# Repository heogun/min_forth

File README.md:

# min_forth

Minimal 64x4 (Revision 1.4 Redux) 홈 컴퓨터용 **16비트 Forth 커널**과, 그 하드웨어를 사이클 단위로 재현하는 **Rust 에뮬레이터** 저장소.

## 구성

| 경로 | 내용 |
| --- | --- |
| `minforth/forth/kernel.fs` | Forth 커널 본체. 호스트 Forth가 아니라 프로젝트 전처리기를 쓰는 어셈블리 소스 |
| `minforth/tools/` | C++ 어셈블러(`asm.cpp`), 이미지 빌더(`build.py`), 보조 스크립트 |
| `minforth/test/` | 커널 검증용 `.fs` 프로그램 |
| `minimal64/Revision 1.4 Redux/FLASH Images/` | ISA 결함 3건을 수정한 ROM이 기존 위치에 직접 설치됨. 실행·빌드·검증의 단일 기준 |
| `minredux/` | 외부 crate 의존성 없는 흑백 기준 Rust 에뮬레이터, ISA/화면 회귀 스크립트 |
| `minredux/gui/` | `minredux` 코어를 사용해 400x240 VRAM을 직접 렌더링하는 창 기반 흑백 프론트엔드 |
| `minredux-cs/` | 컬러 + SN76489 통합안(CS-DRAFT-1)용 Rust 에뮬레이터. `minredux/`를 기반으로 확장 |
| `benchmarks/` | Min 인터프리터와 Forth의 동일 알고리즘 실행 비용 비교 하네스 |
| `AGENTS.md` | 작업 공간 규칙과 커널 불변식 |
| `PROGRESS.md`, `benchmark.md` | 구현 이력, 벤치마크 방법과 결과 |

`minimal64/`(수정 ROM·MinOS·마이크로코드)와 `extended-min/`(별도 Min 인터프리터)은 각자의 저장소에서 관리되며 이 저장소에는 포함하지 않는다. 삭제된 원본 ROM이나 별도 `roms/` 번들은 필요 없다. 위 기본 경로에 수정 이미지와 일치하는 CSV가 있어야 하며 `python3 minredux/verify_rom.py`로 검증한다.

## 빌드

```sh
# 네이티브 어셈블러 (최초 1회, 또는 asm.cpp 수정 후)
clang++ -O2 -std=c++11 minforth/tools/asm.cpp -o minforth/tools/asm

# Forth 커널 이미지: minforth/build/flash.bin 생성
python3 minforth/tools/build.py minforth/forth/kernel.fs minforth 0x1000
```

`build.py`는 `forth/defs.inc`를 앞에 붙이고 매크로/인클루드를 전개한 뒤, 목적지 인자와 일치하는 `#org`를 요구하고 결과를 MinOS 플래시 파일 시스템에 삽입한다. 참조 ROM을 건드리지 않으려면 `--out DIR`을 쓴다.

## 실행과 검증

```sh
cd minredux
cargo build --release

python3 regress.py                      # 커널 end-to-end 회귀
python3 runline.py ': t 0 10 0 DO I + LOOP . ;' 't'
./target/release/minredux term --rom-dir ../minforth/build   # Ctrl-] 로 종료
```

Python 도우미는 실행 파일과 ROM을 자동으로 다시 빌드하지 않으므로, 어셈블리나 Rust 소스를 고친 뒤에는 위 빌드 단계를 먼저 실행한다.

터미널 대신 실제 400x240 화면을 창에서 보려면 `minredux/gui`를 실행한다.
Enter를 LF `0x0a`, Backspace를 `0x08`로 보내므로 터미널의 CR/DEL 불일치가 없다.

```sh
cd minredux/gui
cargo run --release
cargo run --release -- --rom-dir ../../minforth/build   # Forth 커널
```

컬러·SN76489 통합안은 `cd minredux-cs`에서 같은 방식으로 빌드·회귀하며, 추가로
`--ansi`, `--ppm`, `--wav` 출력을 지원한다. 자세한 내용은
[`minredux-cs/README.md`](minredux-cs/README.md)를 참고한다.

## 문서

- Minimal 64x4 원작자(slu4) 매뉴얼 사본: [`docs/manual.txt`](docs/manual.txt)
- 실물 제작 부품 구매 목록과 주의사항: [`docs/HARDWARE_SHOPPING.md`](docs/HARDWARE_SHOPPING.md)
- 커널 설계와 `ABORT"` 동작: [`minforth/README.md`](minforth/README.md)
- 흑백 기준 에뮬레이터 사용법과 정확도 범위: [`minredux/README.md`](minredux/README.md)
- 흑백 GUI 프론트엔드: [`minredux/gui/README.md`](minredux/gui/README.md)
- 컬러·SN76489 에뮬레이터와 한계: [`minredux-cs/README.md`](minredux-cs/README.md)
- ISA 검증 내역: [`minredux/ISA_VALIDATION.md`](minredux/ISA_VALIDATION.md)
- 벤치마크 하네스: [`benchmark.md`](benchmark.md)
- Cycle-exact 제안과 타당성 검토: [`CYCLE_EXACT_ROADMAP.md`](CYCLE_EXACT_ROADMAP.md), [`CYCLE_EXACT_REVIEW.md`](CYCLE_EXACT_REVIEW.md) (구현 승인/실기 검증 완료를 뜻하지 않음)

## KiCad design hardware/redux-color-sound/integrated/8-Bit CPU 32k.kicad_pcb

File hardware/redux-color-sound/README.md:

# Redux 1.4 — Attribute Color + SN76489 통합 보드

상태: **컬러·SN76489 통합 회로도와 PCB 부품/net 배치 초안이 추가됨. 배선·최악 조건 타이밍 검증 미완료, 제조 금지.**

실제 추가 회로와 현재 검증 상태: **[CIRCUIT.md](CIRCUIT.md)**.
KiCad에서는 `integrated/8-Bit CPU 32k.kicad_pro`를 연다.
`cad/`는 경고를 해결한 기존 흑백 보드 기준본이며, 추가 회로가 있는 프로젝트와 구분한다.

2026-10-30 사용자 선택: 기존 Revision 1.4 Redux를 기반으로 컬러와
SN76489 음원을 하나의 새 PCB에 통합한다. 원본 `minimal64/`는 변경하지 않는다.
이 문서는 실기 동작, 타이밍 여유, 제조 가능성을 보증하지 않는다.

## 1. 범위와 불변 조건

- CPU 8MHz, 기존 명령·마이크로코드 실행 사이클을 유지한다.
- 컬러·음원 때문에 CPU 클록을 게이팅하거나 WAIT/DMA를 추가하지 않는다.
- 기존 비트맵 접근 대역폭을 색상 읽기로 나눠 쓰지 않는다.
- 400×240 표시, 기존 PS/2·UART·확장 포트를 유지한다.
- 컬러는 1bpp 비트맵 + 영역별 전경/배경 각 16색이다. 픽셀별 독립 4bpp가 아니다.
- 음원은 SN76489 계열 전용 IC를 사용한다. AY, TTS, SD, 조이스틱은 이번 범위 밖이다.
- DIP/관통형 중심을 유지하되, 정확한 주문번호·소켓·풋프린트는 회로도 확정 후 결정한다.
- 리셋 중/후 컬러 비활성 및 하드웨어 오디오 mute를 목표로 한다.

무대기 CPU와 무제한 주변장치 쓰기는 다르다. 음원·Attribute 쓰기 간격과
pending 데이터의 수명은 소프트웨어가 지켜야 한다. 폴링·지연 명령을 사용하면
그 프로그램의 CPU 시간은 소비된다. 모든 전송을 CPU 비용 없이 처리한다는 뜻이 아니다.

## 2. 확인한 기준 자료

### Redux

- 로컬 원본 저장소 커밋: `1a59c95695d1a6a6147584465ee87803fe9387da`.
- `minimal64/Revision 1.4 Redux/Schematics.pdf`: Control Logic, Memory and MAR, VGA.
- `minimal64/Revision 1.4 Redux/KiCAD9/`: 기존 KiCad 9 프로젝트.
- `minimal64/Revision 1.4 Redux/Programs/asm/vga.asm`: ViewPort `0x430c`.
- `minredux/src/lib.rs`: 64바이트 stride, ViewPort `(96,12)`, 400×240 crop.

기존 VGA는 U36 AS6C62256, U35 HC166, U37/U39 HC590, U38/U40/U41 HC574를 쓴다.
영상 읽기 예약 구간과 CPU 영상 쓰기를 유지하면서 색상 RAM을 병렬 읽는 방향이다.
`~VGA_GET` 종료 시 스캔 카운터도 갱신되므로 같은 에지에서 색상을 무심코
래치하면 다음 바이트 주소/현재 픽셀 간 정렬 문제가 생길 수 있다.

### SN76489 참고 보드

[hans61/Minimal-64x4-Expansion](https://github.com/hans61/Minimal-64x4-Expansion),
검토 커밋 `92207bfac9450aeef2b72a4420adfdd4c44e60af`:

- `hardware/Rev.6/README.md`: 주소 배치와 과거 제어 신호 오류 설명.
- `hardware/Rev.7/eagle/expansion-sn76489-kempton-sd-rev7.sch`: Eagle XML의 부품·net 연결 확인.
- `software/sn76489/BirdSound.asm`: 데이터 기록 후 제어 bit 1 assert/deassert 순서 확인.

확인 사항:

- `0xFEE0` 데이터 HC574, `0xFEE2` 제어 HC173, 제어 bit 1로 음원 쓰기를 제어한다.
- 실제 음원 `~CE`는 GND, HC173 Q2를 HC04로 반전한 신호가 `~WE`로 들어간다.
- CPU bit 0은 SN의 **D7**, CPU bit 7은 SN의 **D0**에 연결된다.
  TI 표기의 D0가 MSB이므로 이름만 보고 같은 번호끼리 연결하면 안 된다.
- 원문은 초기 리비전의 HC74 기반 CS 제어에 드문 오류가 있었으며 Rev.6에서
  HC173으로 바꿨다고 설명한다. 이전 회로로 단순화하지 않는다.
- 음원 경로의 부품 종류: HC30, HC04, HC11, HC138, HC574, HC173, SN76489,
  LM386. 다른 기능을 제외해도 **앰프 포함 8개 IC + 발진기 모듈**인 참고 구조다.
  이는 통합 보드의 확정 BOM이나 최소 칩 수 증명이 아니다.
- 4MHz/3.579MHz 별도 발진기와 확장 포트 클록을 선택하는 연결이 있다.
  원본 보드용 소프트웨어의 NOP 시간은 Redux에 그대로 적용하지 않는다.

[TI SN76489AN 데이터시트 사본](https://map.grauw.nl/resources/sound/texas_instruments_sn76489an.pdf):
5V, 최대 4MHz, open-collector READY, 대략 32 입력 클록의 데이터 처리,
D0=MSB를 확인할 기준이다. SN76494 등은 같은 조건으로 대체하지 않는다.
최종 설계 전에 정확한 구매 칩의 데이터시트 전체 타이밍 표/파형을 확인한다.

[michaelkamprath/minimal-64x4-expansion-cards](https://github.com/michaelkamprath/minimal-64x4-expansion-cards)는
TMS5220C 음성 합성·곱셈기·타이머의 참고 자료다. SN 음원이나 컬러 회로의
검증 자료로 취급하지 않는다. 이번 초안에는 외부 회로 파일을 복사하지 않았다.

## 3. 컬러 주소와 화면 좌표

내부 VRAM은 512×256에 해당하는 **16KB** 비트맵 공간이다.
U36의 부품 용량이 32KB인 것과 실제 연결된 주소 공간은 구분한다.
표시/소프트웨어 ViewPort는 그 안의 `(96,12)`에서 시작하는 400×240 영역이다.

Attribute는 64열×32행, **2KB**, 한 바이트에 `background[7:4] | foreground[3:0]`.
별도 SRAM 한 개를 사용하고 CPU RAM/비트맵을 대신 사용하지 않는다.

**권장 주소식: 글자 행과 일치하도록 세로 위상 +4 (mod 256)**

```text
x, y       = 내부 비트맵 좌표 (0..511, 0..255)
attr_x     = x >> 3
attr_y     = ((y + 4) & 255) >> 3
attr_index = attr_y * 64 + attr_x       # 0..2047

ViewPort 글자 (column, row), column=0..49, row=0..29:
attr_index = (row + 2) * 64 + column + 12
```

이렇게 하면 400×240 화면의 50×30개 8×8 글자 영역과 색상이 일치한다.
보이는 1,500개 Attribute는 2KB 배열 안에서 stride 64로 배치된다.
자동으로 연속된 1,500바이트가 되는 것은 아니다.

단순히 `y >> 3`만 배선하면 ViewPort가 y=12에서 시작하기 때문에 31개
Attribute 행에 걸치고 글자 중간에서 색이 바뀐다. 앞선 단순 50×30 설명에는
이 위상 보정 조건이 빠져 있었다. 보정 로직의 지연·칩 수를 BOM에 포함해야 한다.

### 영상 데이터 경로

```text
스캔 주소 ─┬─ 기존 VRAM → 기존 HC166 → pixel ──────────┐
           └─ Attribute 주소 → SRAM → 색상 레지스터 ──┤
                                                     ↓
                                    전경/배경 선택 → blanking → RGB DAC
CPU → 주소/데이터 유지 → 영상 읽기 외 구간에 Attribute 쓰기
```

- SRAM 읽기는 기존 비트맵 읽기와 병렬 수행한다. 픽셀마다 SRAM을 읽지 않는다.
- 색상 레지스터는 CPU SRAM 쓰기 중에도 현재 출력 색상을 유지한다.
- 읽기/쓰기 주소 MUX, 데이터 래치, pending 제어가 필요하다.
- 새 Attribute 요청이 미처리 요청을 덮어쓰지 않도록 최소 간격 또는 상태 읽기를 정의한다.
- CPU 쓰기 시점과 SRAM commit이 달라질 경우 주소와 데이터가 함께 보존되어야 한다.
- 실제 추가 회로는 기존 VREG의 주소·데이터 유지 및 영상 쓰기 slot을 공유한다.
  제어 bit 2로 비트맵/Attribute 쓰기를 선택하고, 쓰기 캡처 시 plane도 함께 저장한다.
- SRAM 전원 투입 내용은 미정이다. 초기화 전에는 컬러 출력을 활성화하지 않는다.
- 비표시 구간은 모든 RGB를 검정으로 강제한다. HSYNC/VSYNC만으로 active-video를
  판정하거나 기존 VRAM의 0 데이터를 검정 대신 사용하지 않는다.
- ViewPort 외 테두리 색상을 허용할지는 미정이다. 400×240 crop을 곧바로
  회로의 실제 수평·수직 blanking 경계라고 가정하지 않는다.
- RGBI 계열 고정 16색 DAC를 기본 후보로 한다. CGA의 정확한 갈색 보정/색상표
  호환은 아직 약속하지 않는다. 75Ω 부하에서 0..약 0.7V를 검증해야 한다.

## 4. SN76489 데이터 경로

```text
CPU BUS → HC574 데이터 래치 → SN76489 → AC 결합/볼륨 → 오디오 출력
CPU 제어 쓰기 → 리셋 가능한 제어 레지스터 → ~WE
독립 발진기 → SN CLK
```

- 5V DIP-16 SN76489AN을 우선 검토 대상으로 한다. 계열 내 다른 칩은 재검토한다.
- 독립 **3.579545MHz 발진기**를 우선 후보로 한다. 4MHz 기준 음악 데이터는
  음높이 값을 변환해야 한다. 기존 CPU 클록선을 음원 부하로 직접 사용하지 않는다.
- `f = clock / (32 * N)`, 일반 톤 주기 `N=1..1023`. N=0 및 잡음 동작은 별도 검증한다.
- 데이터 유지 → 쓰기 assert → 처리 완료 → 쓰기 deassert → 다음 데이터 순서로 제어한다.
- 약 32클록은 설계 참고값일 뿐 보증 최대 지연이 아니다. 정확한 칩의 READY/파형과
  여유를 검토해 쓰기 폭 및 다음 전송 조건을 확정한다.
- READY를 CPU 클록/WAIT에 연결하지 않는다. 사용한다면 pull-up 및 TTL→HC 입력
  임계값 적합성을 확인하고, 소프트웨어 상태 입력으로 읽도록 한다.
- 단일 래치는 FIFO가 아니다. 전송 중 데이터 갱신 금지 조건을 드라이버에 명시한다.
- SN에는 시스템 reset으로 모든 음량을 확실히 지우는 인터페이스가 없으므로,
  부팅 시 소프트웨어가 `0x9f, 0xbf, 0xdf, 0xff`를 보내기 전까지 아날로그 경로를
  하드웨어 mute한다. 제어 래치만 초기화해서 무음을 보장한다고 주장하지 않는다.
- 기본 출력은 외부 앰프에 연결 가능한 오디오 출력을 우선 검토한다.
  온보드 LM386 스피커 앰프는 선택 실장 후보이며, 헤드폰 출력과 동일시하지 않는다.

## 5. 주소 배치 — 추가 회로 초안

기존 참고 보드와의 음원 제어 관례를 일부 유지할 후보:

| 주소 | 후보 역할 |
| --- | --- |
| `0xFEE0` | 음원 데이터 래치 |
| `0xFEE1` | 상태 읽기 — READY/Attribute mode/color enable/audio enable |
| `0xFEE2` | 제어 레지스터 — bit 0 컬러, bit 1 음원 write, bit 2 Attribute mode, bit 3 unmute |
| `0xFEE3` | 미할당, 참고 보드 SPI와 겹치므로 함부로 재사용하지 않음 |
| `0xFEE4` | 예약 — 초기의 간접 주소 포트안은 채택하지 않음 |
| `0xFEE5` | 예약 |
| `0xFEE6` | 예약 |
| `0xFEE7` | 미할당 |

- 자동 증가·Attribute CPU read-back은 기본 요구사항에 넣지 않는다. 필요 시 비용 평가한다.
- `0xFEE8..0xFEEF`는 bit 3 미디코딩 alias다. 실제 RAM 제외 범위는 `0xFEE0..0xFEEF`다.
- 초기안과 달리 Attribute는 제어 bit 2를 설정하고 기존 `0x4000..0x7fff` VREG 창으로 쓴다.
- MinOS·Forth dictionary/프로그램은 I/O 16바이트를 RAM으로 사용하면 안 된다.
  새 메모리맵의 펌웨어 지원은 아직 추가하지 않았다. 에뮬레이터는
  `minredux-cs/`에 디지털 모델로 추가했다.
- 외부 확장 카드가 같은 주소를 선택하면 충돌한다. 온보드 I/O disable 수단을 고려한다.

## 6. 배치·검증 조건

- Attribute SRAM/색상 래치는 VGA 가까이, 음원/아날로그 출력은 보드 가장자리에 배치한다.
- CPU critical path는 유지하고 신규 팬아웃의 용량·배선 길이를 평가한다.
- 각 IC에 로컬 decoupling, 음원/앰프에는 적절한 bulk capacitor와 전원 필터를 둔다.
  아날로그/디지털 접지면을 무조건 분리하지 말고 연속된 귀환 경로를 확보한다.
- 신규 참조번호는 원본 IC와 충돌하지 않는 범위로 배정한다. 원본 번호는 가능한 보존한다.
- CPU 클록, VGA_GET, SRAM WE/OE, 색상 latch clock, pixel, SN clock/WE/READY에 테스트 포인트.
- 리셋·브라운아웃·부분 실장 시 컬러/mute 상태를 검증한다.
- 수정 제어 ROM 경로/검증은 기존 `docs/HARDWARE_SHOPPING.md`를 따른다.

### 제조 전 통과해야 할 항목

1. 실제 회로도와 정확한 부품/데이터시트/풋프린트 확정.
2. 주소 decode·INH·bank·버스 방향/tri-state truth table 검증.
3. SRAM 주소 MUX→읽기→색상 latch와 카운터 전환의 worst-case setup/hold 계산.
4. 비트맵과 색상의 첫/마지막 픽셀 정렬, Attribute 행 위상, blanking 검증.
5. Attribute 쓰기 중 표시 안정성·요청 유실·최대 갱신율 검증.
6. SN 쓰기 타이밍, 데이터 bit 순서, TTL/CMOS 경계, 리셋 mute 검증.
7. 에뮬레이터/논리 모델 확장 및 기존 CPU 회귀 검사. 이것만으로 전기 검증을 대체하지 않음.
8. KiCad ERC/DRC, netlist 대조, 커넥터·패키지 치수 검사.
9. 전류 예산, VGA 75Ω 출력, 오디오 출력 부하 검토.
10. 시제품에서 오실로스코프 실측과 장시간 CPU/영상/음원 동시 동작 시험.

첫 주문은 검증용 시제품이다. 실기 시험 전 상태를 양산 검증 완료로 표시하지 않는다.

## 7. 현재 산출물과 남은 작업

- 완료: 요구사항, 참고 net 연결 검토, 좌표 보정식, 주소/인터페이스 후보 정리.
- 완료: [수정 CAD 작업본](cad/PROVENANCE.md)의 ERC·DRC·패리티 0건,
  기존 DRC 제외 항목 제거, 원본 회로 연결·동박 형상 보존 검사.
  KiCad에서는 `cad/8-Bit CPU 32k.kicad_pro`를 연다.
- 완료: 실제 통합 회로도 5개 sheet, PCB 부품·pad/net 반영, 추가 BOM 초안,
  디지털/정적 테스트 33개. 주소 디코드는 ATF22V10C 한 개(U64)로 바꿨다. Attribute 행 주소는 VA 버스 앞에서 계산한다(U66, R37–R41). 클록은 U67/U68로 분리했다. [현재 상태](CIRCUIT.md)를 참고한다.
- 에뮬레이터 기준 완료: Forth 커널 단어(`COLOR`, `AUDIO`, `ATTR!`, `ATTRFILL`, `SN!`,
  `TONE`, `VOL`, `NOISE`, `SILENCE`). [`../../minforth/README.md`](../../minforth/README.md)를 참고한다.
  `CIRCUIT.md`의 SN 쓰기 순서를 따르며, 실제 칩 타이밍으로는 검증하지 않았다.
- 타이밍 검토(2026-11-24): [TIMING_REVIEW.md](TIMING_REVIEW.md). 디코드 경로와 Attribute 주소 경로를
  고친 뒤 다시 계산해야 한다.
- 미완료: 추가 회로 배선, 최종 배치, 수정 회로의 타이밍 재검증,
  MinOS 수준 지원 및 실기 검증. 에뮬레이터 디지털 모델은
  [`../../minredux-cs/`](../../minredux-cs/)에 추가했으며, 이는 회로·실기 검증을
  대체하지 않는다.
- KiCad 10.0.7 설치 후 원본 CAD의 ERC/DRC/회로도 parity 기준 검사를 실행했다.
  결과와 재현 방법은 [KICAD_BASELINE.md](KICAD_BASELINE.md)를 참고한다.
  수정 기준 작업본도 같은 도구로 검사했다. 통합 회로도·PCB 검증이나 제조 출력이 완료된 것은 아니다.
- 원본 보드 회로도에 표기된 CC BY-NC-SA 4.0 고지와 외부 프로젝트의 권리 조건을
  파생 CAD 배포 전에 확인·보존한다. hans61 저장소의 공개 접근을 재배포 허가로
  간주하지 않는다. 라이선스 확인 전 회로 파일을 통째로 복사해 배포하지 않는다.

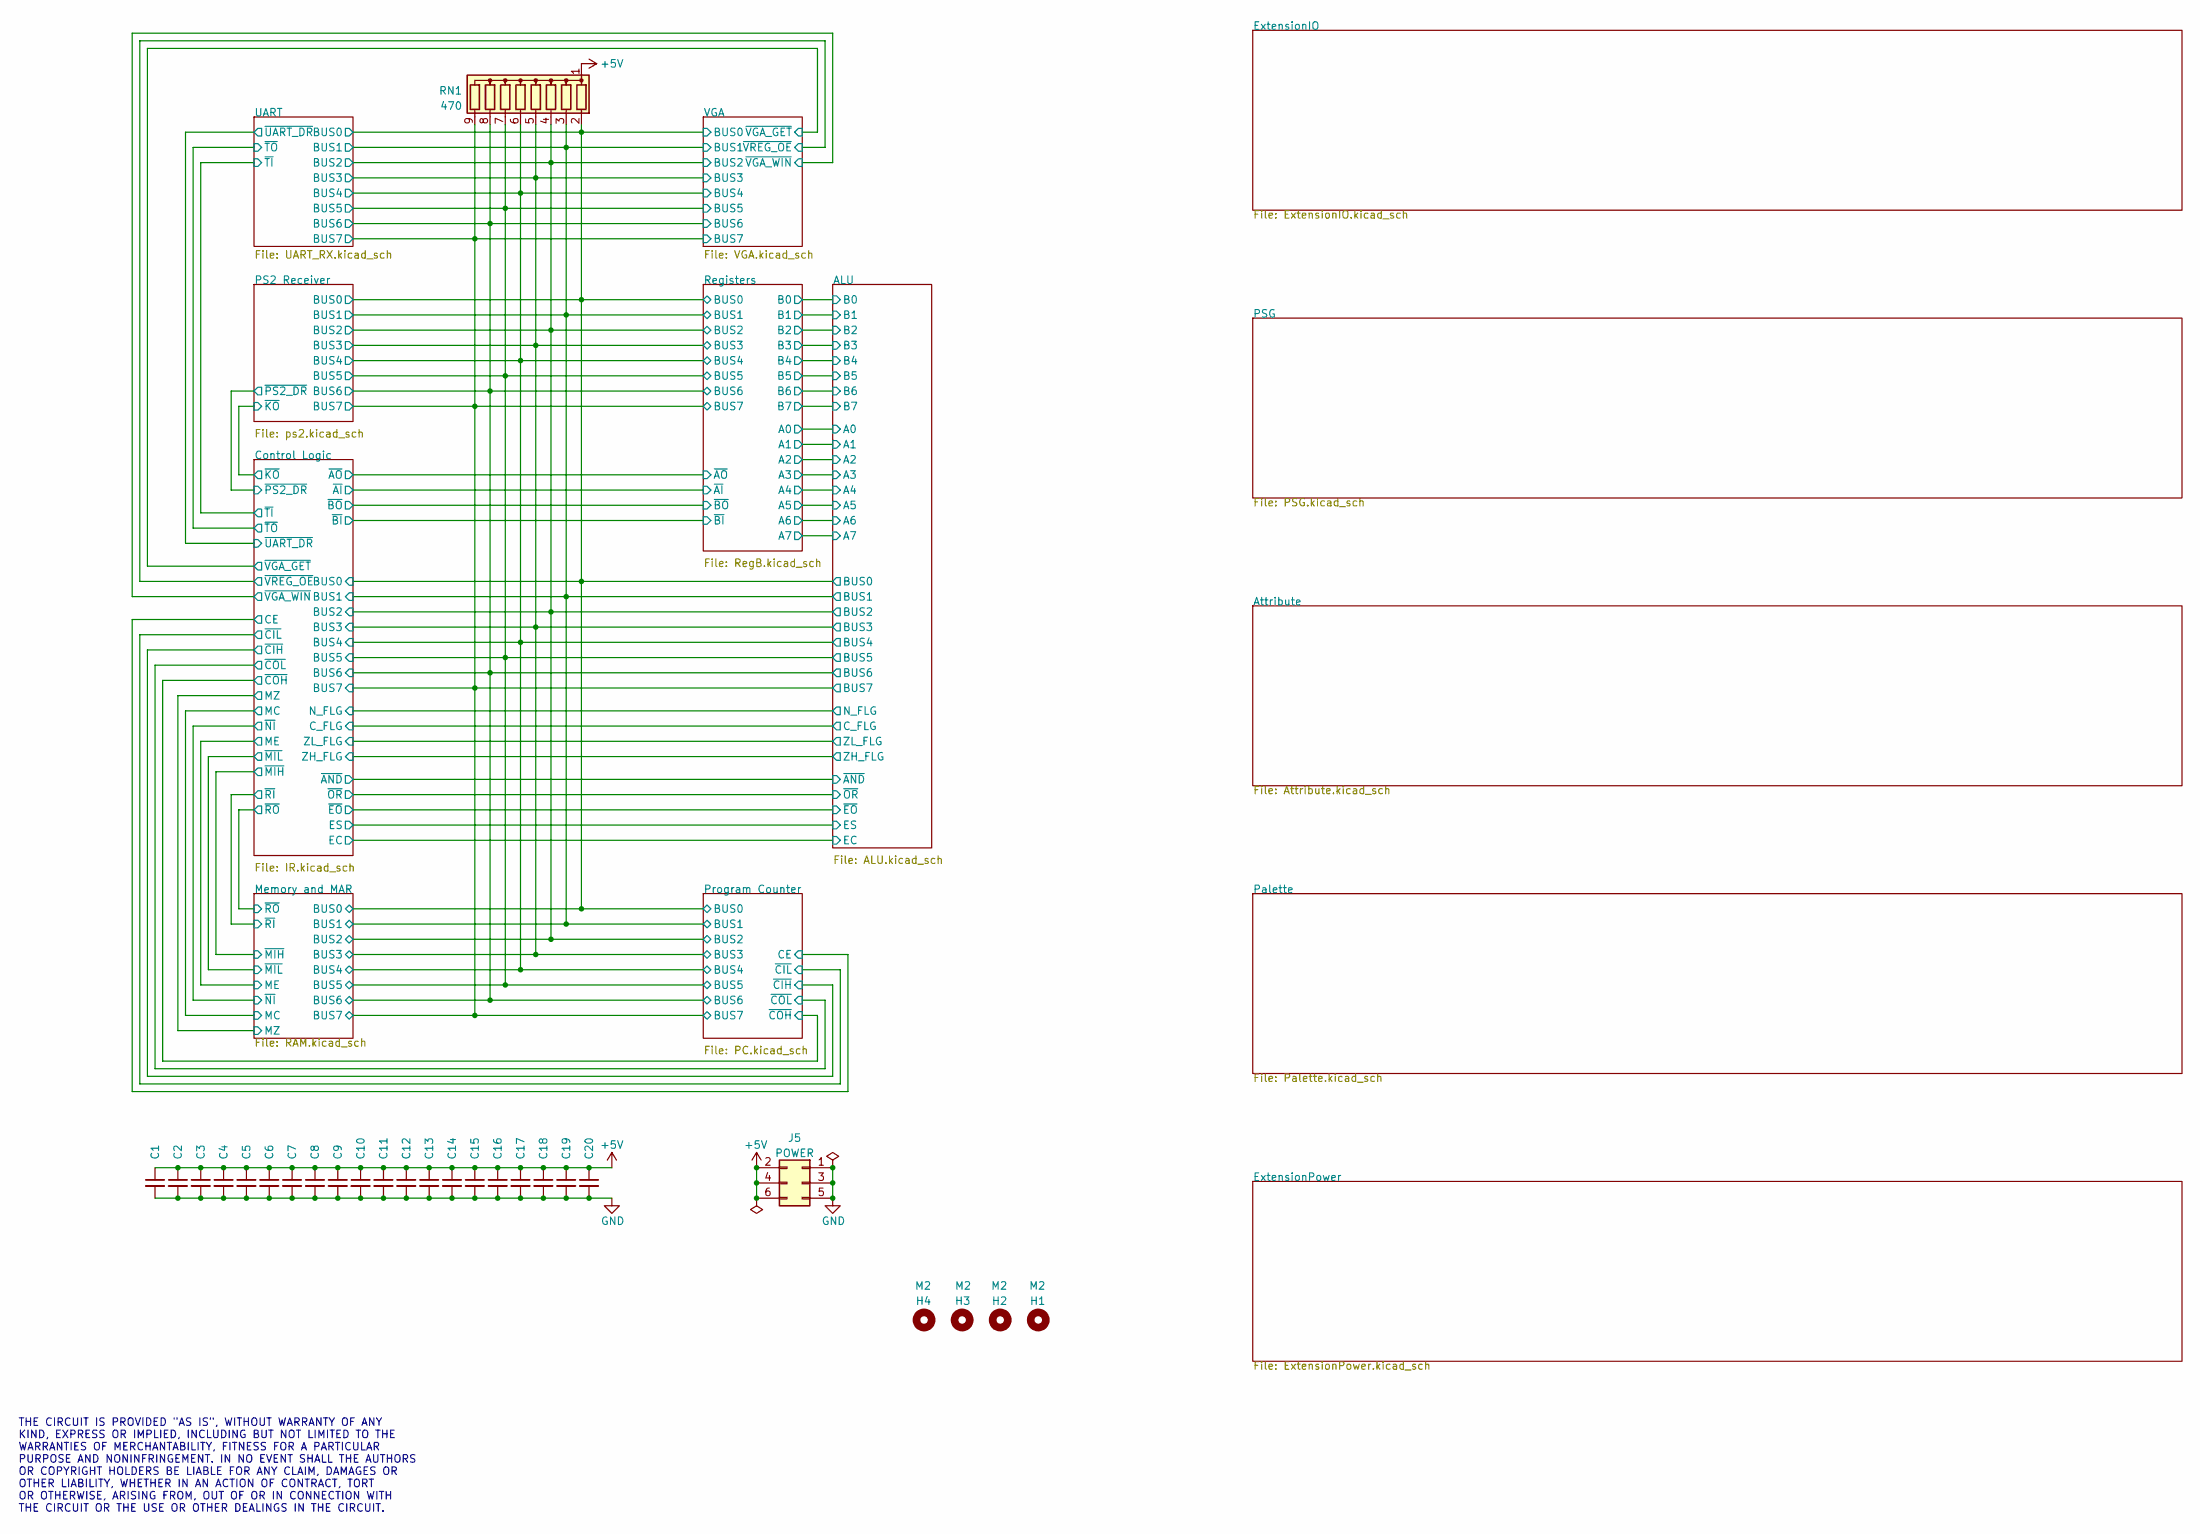
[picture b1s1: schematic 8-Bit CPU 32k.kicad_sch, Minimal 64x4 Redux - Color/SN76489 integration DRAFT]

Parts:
C1, C2, C3, C4, C5, C6, C7, C8, C9, C10, C11, C12, C13, C14, C15, C16, C17, C18, C19, C20: 100nF; C_Disc_D3.4mm_W2.1mm_P2.50mm
H1, H2, H3, H4: M2; MountingHole_2.2mm_M2
J5: POWER; PinSocket_2x03_P2.54mm_Vertical
RN1: 470; R_Array_SIP9

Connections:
+5V: C1.1, C2.1, C3.1, C4.1, C5.1, C6.1, C7.1, C8.1, C9.1, C10.1, C11.1, C12.1, C13.1, C14.1, C15.1, C16.1, C17.1, C18.1, C19.1, C20.1, J5.2, J5.4, J5.6, RN1.1 (common); also elsewhere on the board
BUS0: RN1.2 (R1); also elsewhere on the board
BUS1: RN1.3 (R2); also elsewhere on the board
BUS2: RN1.4 (R3); also elsewhere on the board
BUS3: RN1.5 (R4); also elsewhere on the board
BUS4: RN1.6 (R5); also elsewhere on the board
BUS5: RN1.7 (R6); also elsewhere on the board
BUS6: RN1.8 (R7); also elsewhere on the board
BUS7: RN1.9 (R8); also elsewhere on the board
GND: C1.2, C2.2, C3.2, C4.2, C5.2, C6.2, C7.2, C8.2, C9.2, C10.2, C11.2, C12.2, C13.2, C14.2, C15.2, C16.2, C17.2, C18.2, C19.2, C20.2, J5.1, J5.3, J5.5; also elsewhere on the board

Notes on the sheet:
THE CIRCUIT IS PROVIDED "AS IS", WITHOUT WARRANTY OF ANY KIND, EXPRESS OR IMPLIED, INCLUDING BUT NOT LIMITED TO THE WARRANTIES OF MERCHANTABILITY, FITNESS FOR A PARTICULAR PURPOSE AND NONINFRINGEMENT. IN NO EVENT SHALL THE AUTHORS OR COPYRIGHT HOLDERS BE LIABLE FOR ANY CLAIM, DAMAGES OR OTHER LIABI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

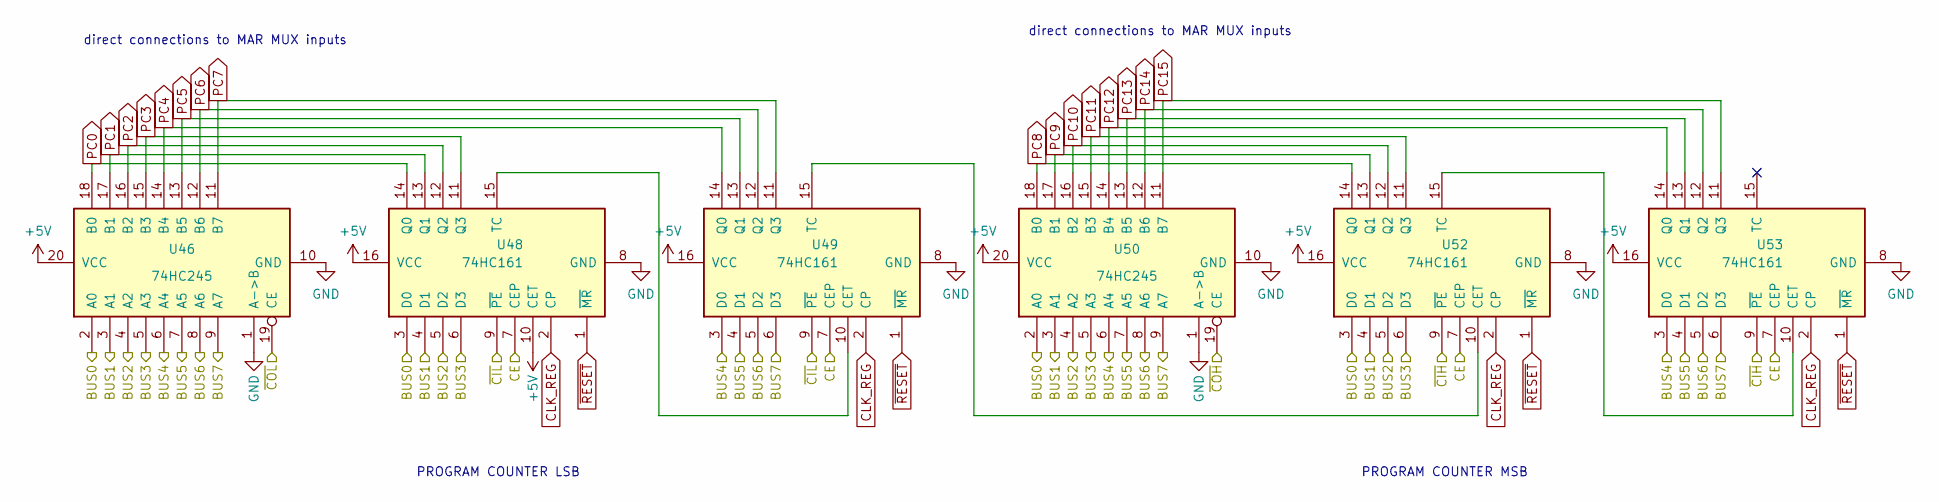
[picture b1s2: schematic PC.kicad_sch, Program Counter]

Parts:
U46, U50: 74HC245; DIP-20_W7.62mm_Socket
U48, U49, U52, U53: 74HC161; DIP-16_W7.62mm_Socket

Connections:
+5V: U46.20 (VCC), U48.10 (CET), U48.16 (VCC), U49.16 (VCC), U50.20 (VCC), U52.16 (VCC), U53.16 (VCC); also elsewhere on the board
/Control Logic/CE: U48.7 (CEP), U49.7 (CEP), U52.7 (CEP), U53.7 (CEP); also elsewhere on the board
/Control Logic/~CIH: U52.9 (~PE), U53.9 (~PE); also elsewhere on the board
/Control Logic/~CIL: U48.9 (~PE), U49.9 (~PE); also elsewhere on the board
/Control Logic/~COH: U50.19 (CE); also elsewhere on the board
/Control Logic/~COL: U46.19 (CE); also elsewhere on the board
BUS0: U46.2 (A0), U48.3 (D0), U50.2 (A0), U52.3 (D0); also elsewhere on the board
BUS1: U46.3 (A1), U48.4 (D1), U50.3 (A1), U52.4 (D1); also elsewhere on the board
BUS2: U46.4 (A2), U48.5 (D2), U50.4 (A2), U52.5 (D2); also elsewhere on the board
BUS3: U46.5 (A3), U48.6 (D3), U50.5 (A3), U52.6 (D3); also elsewhere on the board
BUS4: U46.6 (A4), U49.3 (D0), U50.6 (A4), U53.3 (D0); also elsewhere on the board
BUS5: U46.7 (A5), U49.4 (D1), U50.7 (A5), U53.4 (D1); also elsewhere on the board
BUS6: U46.8 (A6), U49.5 (D2), U50.8 (A6), U53.5 (D2); also elsewhere on the board
BUS7: U46.9 (A7), U49.6 (D3), U50.9 (A7), U53.6 (D3); also elsewhere on the board
CLK_REG: U48.2 (CP), U49.2 (CP), U52.2 (CP), U53.2 (CP); also elsewhere on the board
GND: U46.1 (A->B), U46.10 (GND), U48.8 (GND), U49.8 (GND), U50.1 (A->B), U50.10 (GND), U52.8 (GND), U53.8 (GND); also elsewhere on the board
unnamed: U48.15 (TC), U49.10 (CET)
unnamed: U49.15 (TC), U52.10 (CET)
unnamed: U52.15 (TC), U53.10 (CET)
PC0: U46.18 (B0), U48.14 (Q0); also elsewhere on the board
PC1: U46.17 (B1), U48.13 (Q1); also elsewhere on the board
PC2: U46.16 (B2), U48.12 (Q2); also elsewhere on the board
PC3: U46.15 (B3), U48.11 (Q3); also elsewhere on the board
PC4: U46.14 (B4), U49.14 (Q0); also elsewhere on the board
PC5: U46.13 (B5), U49.13 (Q1); also elsewhere on the board
PC6: U46.12 (B6), U49.12 (Q2); also elsewhere on the board
PC7: U46.11 (B7), U49.11 (Q3); also elsewhere on the board
PC8: U50.18 (B0), U52.14 (Q0); also elsewhere on the board
PC9: U50.17 (B1), U52.13 (Q1); also elsewhere on the board
PC10: U50.16 (B2), U52.12 (Q2); also elsewhere on the board
PC11: U50.15 (B3), U52.11 (Q3); also elsewhere on the board
PC12: U50.14 (B4), U53.14 (Q0); also elsewhere on the board
PC13: U50.13 (B5), U53.13 (Q1); also elsewhere on the board
PC14: U50.12 (B6), U53.12 (Q2); also elsewhere on the board
PC15: U50.11 (B7), U53.11 (Q3); also elsewhere on the board
~RESET: U48.1 (~MR), U49.1 (~MR), U52.1 (~MR), U53.1 (~MR); also elsewhere on the board

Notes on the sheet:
PROGRAM COUNTER MSB
PROGRAM COUNTER LSB
direct connections to MAR MUX inputs

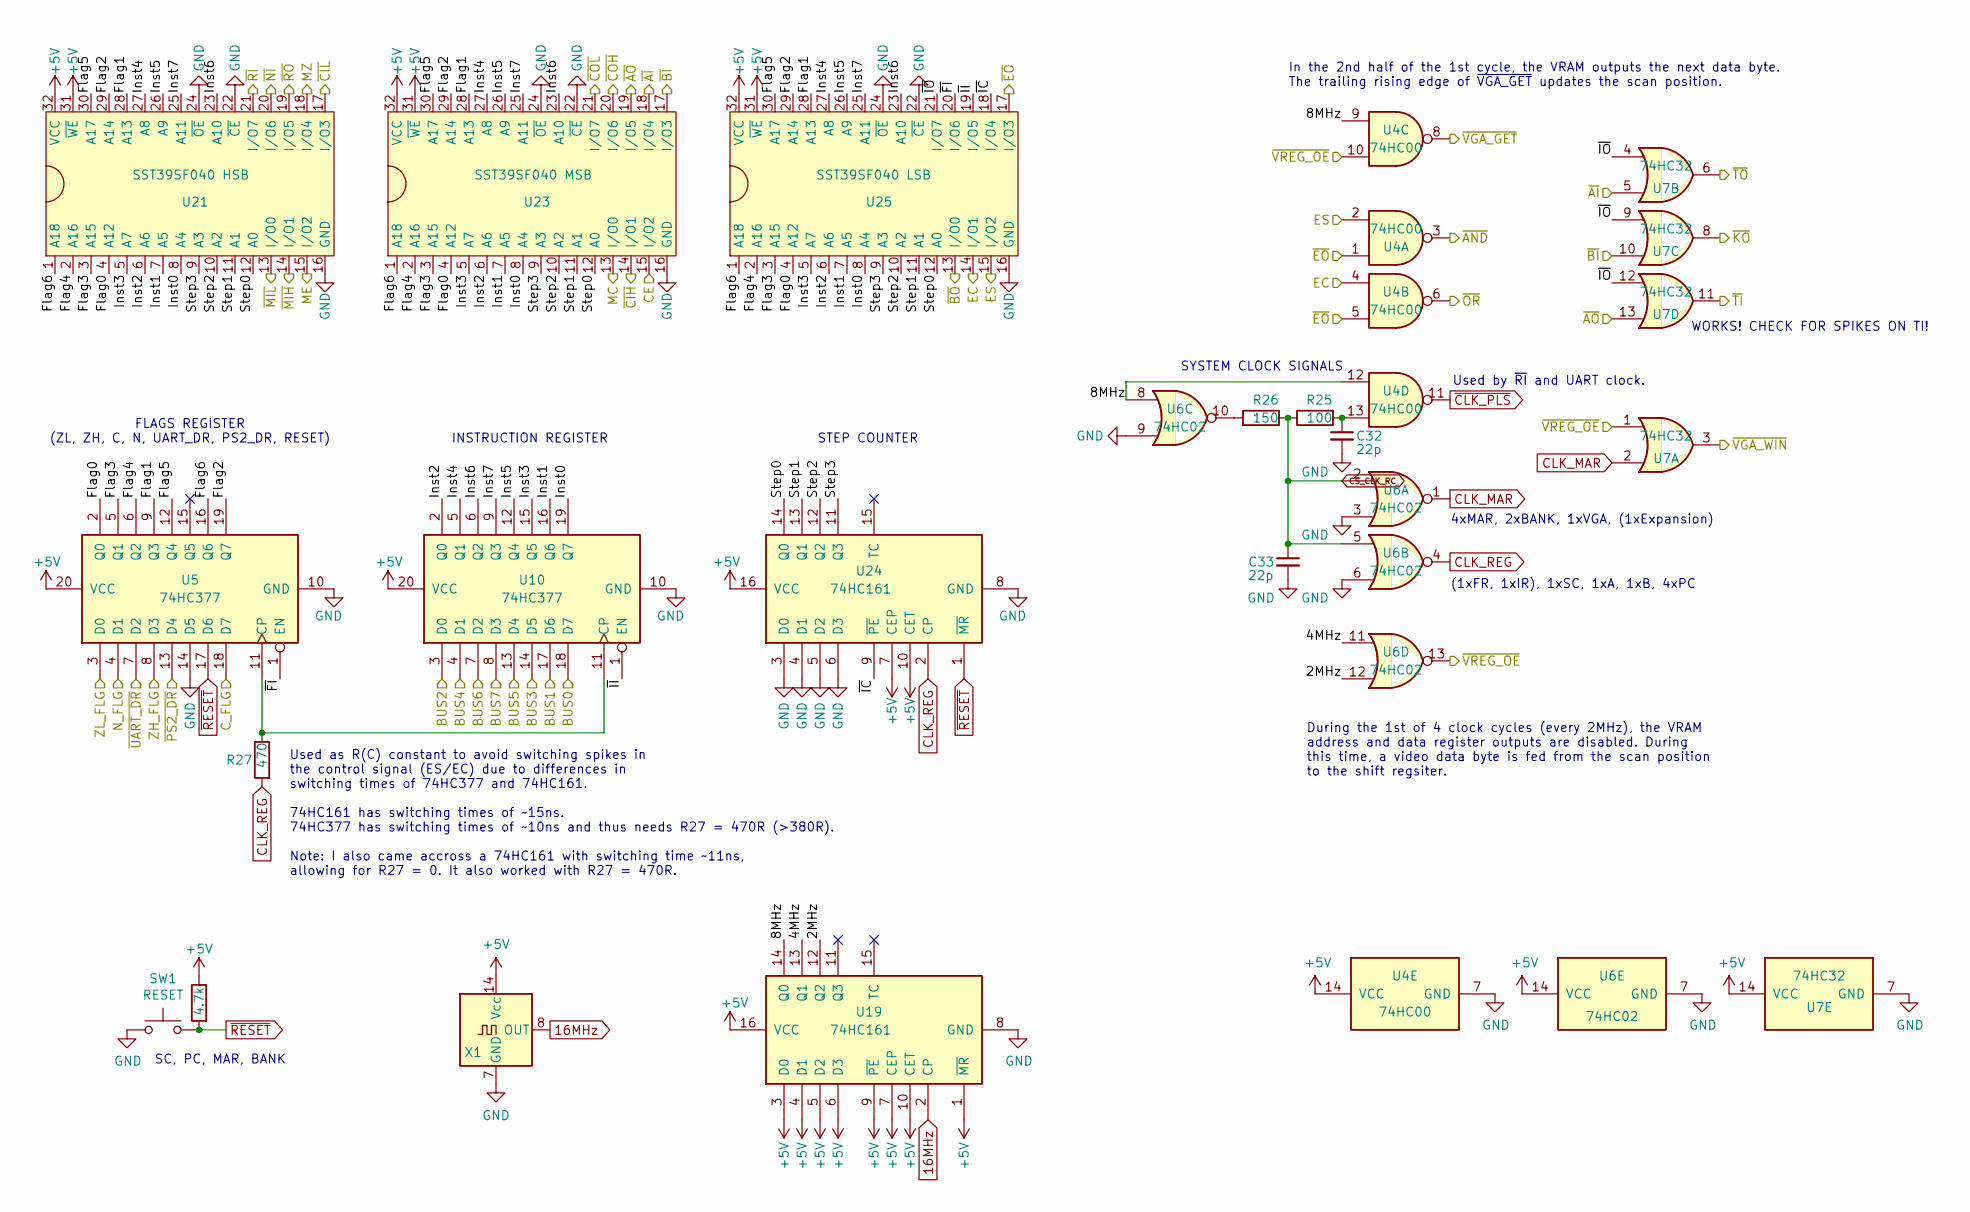
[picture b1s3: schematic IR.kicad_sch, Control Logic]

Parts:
C32, C33: 22p; C_Disc_D3.4mm_W2.1mm_P2.50mm
R2: 4.7k; R_Axial_DIN0207_L6.3mm_D2.5mm_P7.62mm_Horizontal
R25: 100; R_Axial_DIN0207_L6.3mm_D2.5mm_P7.62mm_Horizontal
R26: 150; R_Axial_DIN0207_L6.3mm_D2.5mm_P7.62mm_Horizontal
R27: 470; R_Axial_DIN0207_L6.3mm_D2.5mm_P7.62mm_Horizontal
SW1: RESET; SW_PUSH_6mm
U4: 74HC00; DIP-14_W7.62mm_Socket
U5, U10: 74HC377; DIP-20_W7.62mm_Socket
U6: 74HC02; DIP-14_W7.62mm_Socket
U7: 74HC32; DIP-14_W7.62mm_Socket
U19, U24: 74HC161; DIP-16_W7.62mm_Socket
U21: SST39SF040 HSB; DIP-32_W15.24mm_Socket
U23: SST39SF040 MSB; DIP-32_W15.24mm_Socket
U25: SST39SF040 LSB; DIP-32_W15.24mm_Socket
X1: 16MHz; Oscillator_DIP-14

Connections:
16MHz: U19.2 (CP), X1.8 (OUT); also elsewhere on the board
+5V: R2.1, U4.14 (VCC), U5.20 (VCC), U6.14 (VCC), U7.14 (VCC), U10.20 (VCC), U19.1 (~MR), U19.3 (D0), U19.4 (D1), U19.5 (D2), U19.6 (D3), U19.7 (CEP), U19.9 (~PE), U19.10 (CET), U19.16 (VCC), U21.31 (~WE), U21.32 (VCC), U23.31 (~WE), U23.32 (VCC), U24.7 (CEP), U24.10 (CET), U24.16 (VCC), U25.31 (~WE), U25.32 (VCC), X1.14 (Vcc); also elsewhere on the board
/ALU/C_FLG: U5.18 (D7); also elsewhere on the board
/ALU/EC: U4.4, U25.14 (I/O1); also elsewhere on the board
/ALU/ES: U4.2, U25.15 (I/O2); also elsewhere on the board
/ALU/N_FLG: U5.4 (D1); also elsewhere on the board
/ALU/ZH_FLG: U5.8 (D3); also elsewhere on the board
/ALU/ZL_FLG: U5.3 (D0); also elsewhere on the board
/ALU/~AND: U4.3; also elsewhere on the board
/ALU/~EO: U4.1, U4.5, U25.17 (I/O3); also elsewhere on the board
/ALU/~OR: U4.6; also elsewhere on the board
/Control Logic/2MHz: U6.12, U19.12 (Q2)
/Control Logic/4MHz: U6.11, U19.13 (Q1)
/Control Logic/8MHz: U4.9, U4.12, U6.8, U19.14 (Q0)
/Control Logic/CE: U23.15 (I/O2); also elsewhere on the board
/Control Logic/Flag0: U5.2 (Q0), U21.4 (A12), U23.4 (A12), U25.4 (A12)
/Control Logic/Flag1: U5.9 (Q3), U21.28 (A13), U23.28 (A13), U25.28 (A13)
/Control Logic/Flag2: U5.19 (Q7), U21.29 (A14), U23.29 (A14), U25.29 (A14)
/Control Logic/Flag3: U5.5 (Q1), U21.3 (A15), U23.3 (A15), U25.3 (A15)
/Control Logic/Flag4: U5.6 (Q2), U21.2 (A16), U23.2 (A16), U25.2 (A16)
/Control Logic/Flag5: U5.12 (Q4), U21.30 (A17), U23.30 (A17), U25.30 (A17)
/Control Logic/Flag6: U5.16 (Q6), U21.1 (A18), U23.1 (A18), U25.1 (A18)
/Control Logic/Inst0: U10.19 (Q7), U21.8 (A4), U23.8 (A4), U25.8 (A4)
/Control Logic/Inst1: U10.16 (Q6), U21.7 (A5), U23.7 (A5), U25.7 (A5)
/Control Logic/Inst2: U10.2 (Q0), U21.6 (A6), U23.6 (A6), U25.6 (A6)
/Control Logic/Inst3: U10.15 (Q5), U21.5 (A7), U23.5 (A7), U25.5 (A7)
/Control Logic/Inst4: U10.5 (Q1), U21.27 (A8), U23.27 (A8), U25.27 (A8)
/Control Logic/Inst5: U10.12 (Q4), U21.26 (A9), U23.26 (A9), U25.26 (A9)
/Control Logic/Inst6: U10.6 (Q2), U21.23 (A10), U23.23 (A10), U25.23 (A10)
/Control Logic/Inst7: U10.9 (Q3), U21.25 (A11), U23.25 (A11), U25.25 (A11)
/Control Logic/MC: U23.13 (I/O0); also elsewhere on the board
/Control Logic/ME: U21.15 (I/O2); also elsewhere on the board
/Control Logic/MZ: U21.18 (I/O4); also elsewhere on the board
/Control Logic/Step0: U21.12 (A0), U23.12 (A0), U24.14 (Q0), U25.12 (A0)
/Control Logic/Step1: U21.11 (A1), U23.11 (A1), U24.13 (Q1), U25.11 (A1)
/Control Logic/Step2: U21.10 (A2), U23.10 (A2), U24.12 (Q2), U25.10 (A2)
/Control Logic/Step3: U21.9 (A3), U23.9 (A3), U24.11 (Q3), U25.9 (A3)
/Control Logic/~AI: U7.5, U23.18 (I/O4); also elsewhere on the board
/Control Logic/~AO: U7.13, U23.19 (I/O5); also elsewhere on the board
/Control Logic/~BI: U7.10, U23.17 (I/O3); also elsewhere on the board
/Control Logic/~BO: U25.13 (I/O0); also elsewhere on the board
/Control Logic/~CIH: U23.14 (I/O1); also elsewhere on the board
/Control Logic/~CIL: U21.17 (I/O3); also elsewhere on the board
/Control Logic/~COH: U23.20 (I/O6); also elsewhere on the board
/Control Logic/~COL: U23.21 (I/O7); also elsewhere on the board
/Control Logic/~FI: U5.1 (EN), U25.20 (I/O6)
/Control Logic/~IC: U24.9 (~PE), U25.18 (I/O4)
/Control Logic/~II: U10.1 (EN), U25.19 (I/O5)
/Control Logic/~IO: U7.4, U7.9, U7.12, U25.21 (I/O7)
/Control Logic/~KO: U7.8; also elsewhere on the board
/Control Logic/~MIH: U21.14 (I/O1); also elsewhere on the board
/Control Logic/~MIL: U21.13 (I/O0); also elsewhere on the board
/Control Logic/~NI: U21.20 (I/O6); also elsewhere on the board
/Control Logic/~PS2_DR: U5.13 (D4); also elsewhere on the board
/Control Logic/~TI: U7.11; also elsewhere on the board
/Control Logic/~TO: U7.6; also elsewhere on the board
/Control Logic/~UART_DR: U5.7 (D2); also elsewhere on the board
/Control Logic/~VGA_WIN: U7.3; also elsewhere on the board
BUS0: U10.18 (D7); also elsewhere on the board
BUS1: U10.17 (D6); also elsewhere on the board
BUS2: U10.3 (D0); also elsewhere on the board
BUS3: U10.14 (D5); also elsewhere on the board
BUS4: U10.4 (D1); also elsewhere on the board
BUS5: U10.13 (D4); also elsewhere on the board
BUS6: U10.7 (D2); also elsewhere on the board
BUS7: U10.8 (D3); also elsewhere on the board
CLK_MAR: U6.1, U7.2; also elsewhere on the board
CLK_REG: R27.2, U6.4, U24.2 (CP); also elsewhere on the board
CS_CLK_RC: C33.1, R25.1, R26.1, U6.2, U6.5; also elsewhere on the board
GND: C32.2, C33.2, SW1.2, U4.7 (GND), U5.10 (GND), U5.14 (D5), U6.3, U6.6, U6.7 (GND), U6.9, U7.7 (GND), U10.10 (GND), U19.8 (GND), U21.16 (GND), U21.22 (~CE), U21.24 (~OE), U23.16 (GND), U23.22 (~CE), U23.24 (~OE), U24.3 (D0), U24.4 (D1), U24.5 (D2), U24.6 (D3), U24.8 (GND), U25.16 (GND), U25.22 (~CE), U25.24 (~OE), X1.7 (GND); also elsewhere on the board
unnamed: C32.1, R25.2, U4.13
unnamed: R26.2, U6.10
unnamed: R27.1, U5.11 (CP), U10.11 (CP)
~CLK_PLS: U4.11; also elsewhere on the board
~RESET: R2.2, SW1.1, U5.17 (D6), U24.1 (~MR); also elsewhere on the board
~RI: U21.21 (I/O7); also elsewhere on the board
~RO: U21.19 (I/O5); also elsewhere on the board
~VGA_GET: U4.8; also elsewhere on the board
~VREG_OE: U4.10, U6.13, U7.1; also elsewhere on the board

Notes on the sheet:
SYSTEM CLOCK SIGNALS
During the 1st of 4 clock cycles (every 2MHz), the VRAM address and data register outputs are disabled. During this time, a video data byte is fed from the scan position to the shift regsiter.
In the 2nd half of the 1st cycle, the VRAM outputs the next data byte. The trailing rising edge of ~{VGA_GET} updates the scan position.
SC, PC, MAR, BANK
Used by ~{RI} and UART clock.
INSTRUCTION REGISTER
4xMAR, 2xBANK, 1xVGA, (1xExpansion)
(1xFR, 1xIR), 1xSC, 1xA, 1xB, 4xPC
STEP COUNTER
Used as R(C) constant to avoid switching spikes in the control signal (ES/EC) due to differences in switching times of 74HC377 and 74HC161. 74HC161 has switching times of ~15ns. 74HC377 has switching times of ~10ns and thus needs R27 = 470R (>380R). Note: I also came accross a 74HC161 with switchin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
FLAGS REGISTER (ZL, ZH, C, N, UART_DR, PS2_DR, RESET)
WORKS! CHECK FOR SPIKES ON TI!

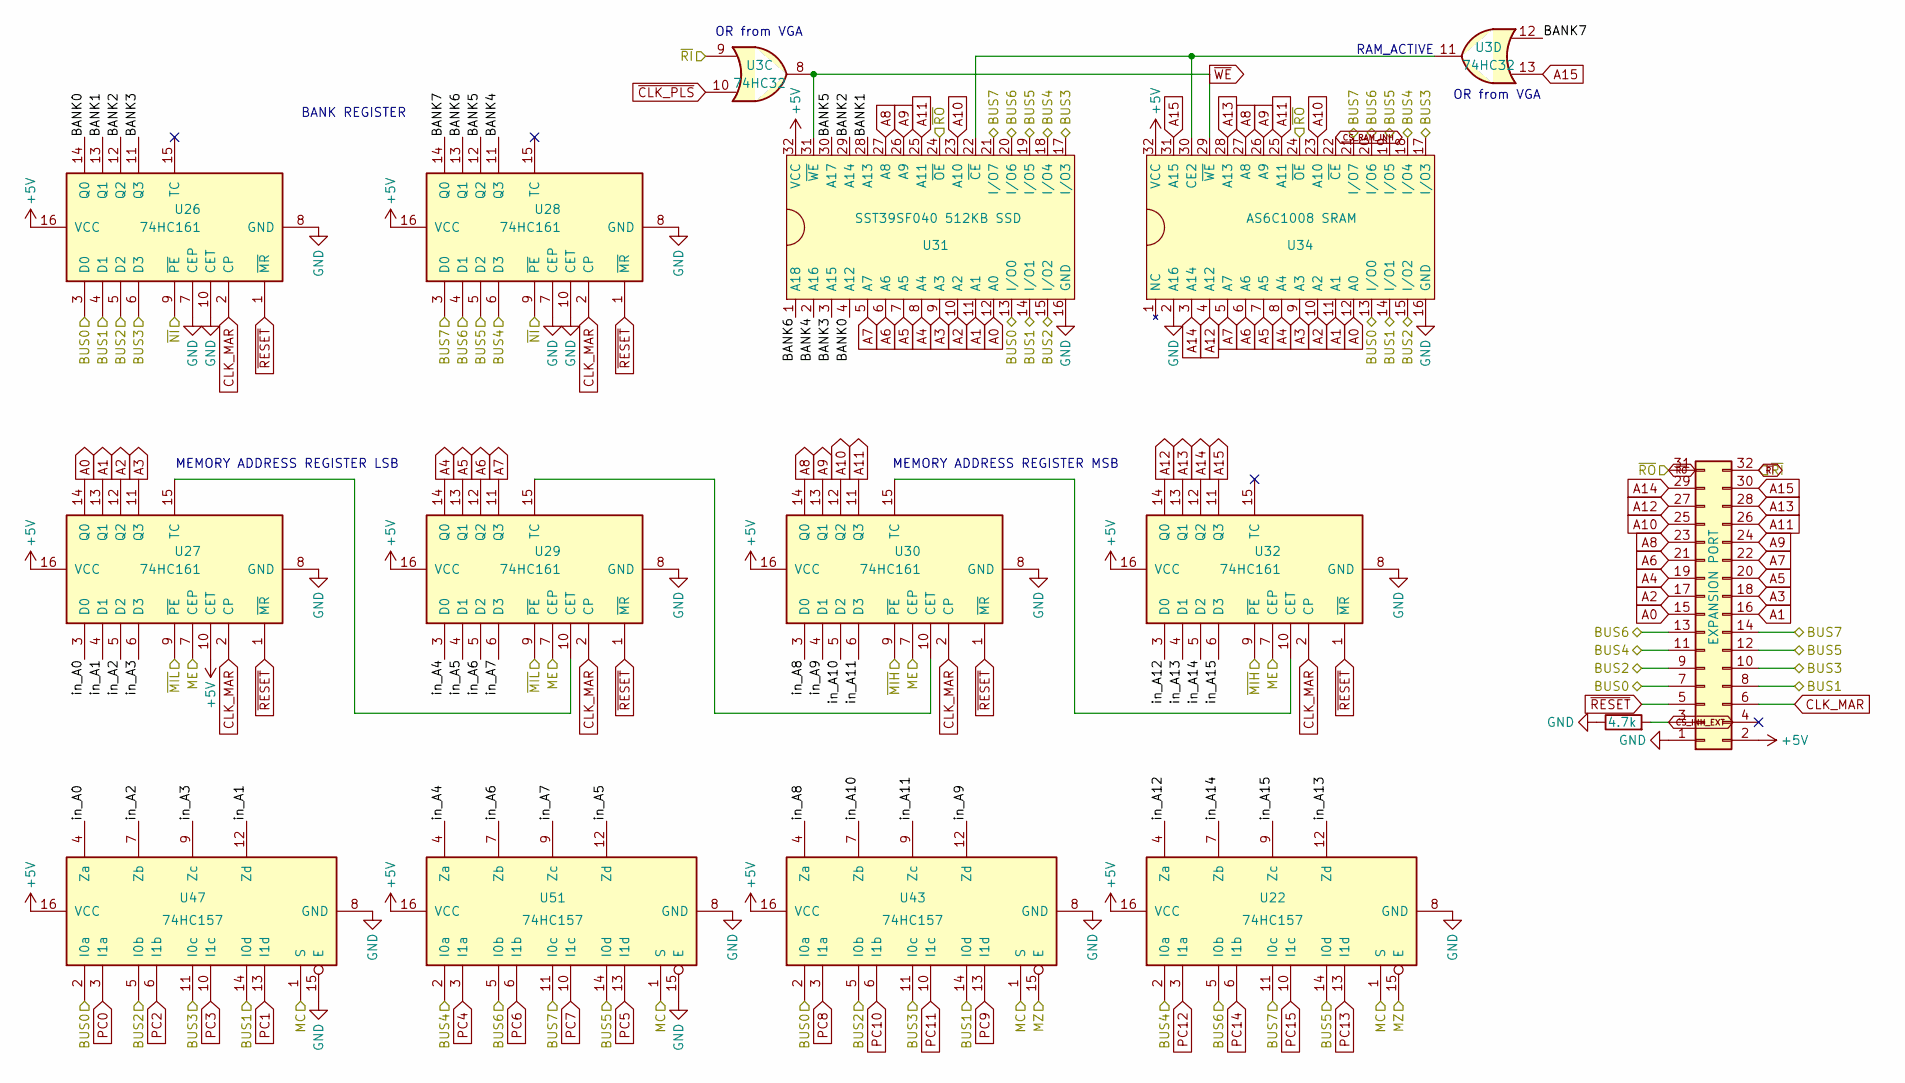
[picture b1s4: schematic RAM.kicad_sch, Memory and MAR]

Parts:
J3: EXPANSION PORT; PinSocket_2x16_P2.54mm_Vertical
R5: 4.7k; R_Axial_DIN0207_L6.3mm_D2.5mm_P7.62mm_Horizontal
U3: 74HC32; DIP-14_W7.62mm_Socket
U22, U43, U47, U51: 74HC157; DIP-16_W7.62mm_Socket
U26, U27, U28, U29, U30, U32: 74HC161; DIP-16_W7.62mm_Socket
U31: SST39SF040 512KB SSD; DIP-32_W15.24mm_Socket
U34: AS6C1008 SRAM; DIP-32_W15.24mm_Socket

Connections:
+5V: J3.2, U22.16 (VCC), U26.16 (VCC), U27.10 (CET), U27.16 (VCC), U28.16 (VCC), U29.16 (VCC), U30.16 (VCC), U31.32 (VCC), U32.16 (VCC), U34.32 (VCC), U43.16 (VCC), U47.16 (VCC), U51.16 (VCC); also elsewhere on the board
/Control Logic/MC: U22.1 (S), U43.1 (S), U47.1 (S), U51.1 (S); also elsewhere on the board
/Control Logic/ME: U27.7 (CEP), U29.7 (CEP), U30.7 (CEP), U32.7 (CEP); also elsewhere on the board
/Control Logic/MZ: U22.15 (E), U43.15 (E); also elsewhere on the board
/Control Logic/~MIH: U30.9 (~PE), U32.9 (~PE); also elsewhere on the board
/Control Logic/~MIL: U27.9 (~PE), U29.9 (~PE); also elsewhere on the board
/Control Logic/~NI: U26.9 (~PE), U28.9 (~PE); also elsewhere on the board
/Memory and MAR/BANK0: U26.14 (Q0), U31.4 (A12)
/Memory and MAR/BANK1: U26.13 (Q1), U31.28 (A13)
/Memory and MAR/BANK2: U26.12 (Q2), U31.29 (A14)
/Memory and MAR/BANK3: U26.11 (Q3), U31.3 (A15)
/Memory and MAR/BANK4: U28.11 (Q3), U31.2 (A16)
/Memory and MAR/BANK5: U28.12 (Q2), U31.30 (A17)
/Memory and MAR/BANK6: U28.13 (Q1), U31.1 (A18)
/Memory and MAR/BANK7: U3.12, U28.14 (Q0)
/Memory and MAR/in_A0: U27.3 (D0), U47.4 (Za)
/Memory and MAR/in_A1: U27.4 (D1), U47.12 (Zd)
/Memory and MAR/in_A2: U27.5 (D2), U47.7 (Zb)
/Memory and MAR/in_A3: U27.6 (D3), U47.9 (Zc)
/Memory and MAR/in_A4: U29.3 (D0), U51.4 (Za)
/Memory and MAR/in_A5: U29.4 (D1), U51.12 (Zd)
/Memory and MAR/in_A6: U29.5 (D2), U51.7 (Zb)
/Memory and MAR/in_A7: U29.6 (D3), U51.9 (Zc)
/Memory and MAR/in_A8: U30.3 (D0), U43.4 (Za)
/Memory and MAR/in_A9: U30.4 (D1), U43.12 (Zd)
/Memory and MAR/in_A10: U30.5 (D2), U43.7 (Zb)
/Memory and MAR/in_A11: U30.6 (D3), U43.9 (Zc)
/Memory and MAR/in_A12: U22.4 (Za), U32.3 (D0)
/Memory and MAR/in_A13: U22.12 (Zd), U32.4 (D1)
/Memory and MAR/in_A14: U22.7 (Zb), U32.5 (D2)
/Memory and MAR/in_A15: U22.9 (Zc), U32.6 (D3)
A0: J3.15, U27.14 (Q0), U31.12 (A0), U34.12 (A0); also elsewhere on the board
A1: J3.16, U27.13 (Q1), U31.11 (A1), U34.11 (A1); also elsewhere on the board
A2: J3.17, U27.12 (Q2), U31.10 (A2), U34.10 (A2); also elsewhere on the board
A3: J3.18, U27.11 (Q3), U31.9 (A3), U34.9 (A3); also elsewhere on the board
A4: J3.19, U29.14 (Q0), U31.8 (A4), U34.8 (A4); also elsewhere on the board
A5: J3.20, U29.13 (Q1), U31.7 (A5), U34.7 (A5); also elsewhere on the board
A6: J3.21, U29.12 (Q2), U31.6 (A6), U34.6 (A6); also elsewhere on the board
A7: J3.22, U29.11 (Q3), U31.5 (A7), U34.5 (A7); also elsewhere on the board
A8: J3.23, U30.14 (Q0), U31.27 (A8), U34.27 (A8); also elsewhere on the board
A9: J3.24, U30.13 (Q1), U31.26 (A9), U34.26 (A9); also elsewhere on the board
A10: J3.25, U30.12 (Q2), U31.23 (A10), U34.23 (A10); also elsewhere on the board
A11: J3.26, U30.11 (Q3), U31.25 (A11), U34.25 (A11); also elsewhere on the board
A12: J3.27, U32.14 (Q0), U34.4 (A12); also elsewhere on the board
A13: J3.28, U32.13 (Q1), U34.28 (A13); also elsewhere on the board
A14: J3.29, U32.12 (Q2), U34.3 (A14); also elsewhere on the board
A15: J3.30, U3.13, U32.11 (Q3), U34.31 (A15); also elsewhere on the board
BUS0: J3.7, U26.3 (D0), U31.13 (I/O0), U34.13 (I/O0), U43.2 (I0a), U47.2 (I0a); also elsewhere on the board
BUS1: J3.8, U26.4 (D1), U31.14 (I/O1), U34.14 (I/O1), U43.14 (I0d), U47.14 (I0d); also elsewhere on the board
BUS2: J3.9, U26.5 (D2), U31.15 (I/O2), U34.15 (I/O2), U43.5 (I0b), U47.5 (I0b); also elsewhere on the board
BUS3: J3.10, U26.6 (D3), U31.17 (I/O3), U34.17 (I/O3), U43.11 (I0c), U47.11 (I0c); also elsewhere on the board
BUS4: J3.11, U22.2 (I0a), U28.6 (D3), U31.18 (I/O4), U34.18 (I/O4), U51.2 (I0a); also elsewhere on the board
BUS5: J3.12, U22.14 (I0d), U28.5 (D2), U31.19 (I/O5), U34.19 (I/O5), U51.14 (I0d); also elsewhere on the board
BUS6: J3.13, U22.5 (I0b), U28.4 (D1), U31.20 (I/O6), U34.20 (I/O6), U51.5 (I0b); also elsewhere on the board
BUS7: J3.14, U22.11 (I0c), U28.3 (D0), U31.21 (I/O7), U34.21 (I/O7), U51.11 (I0c); also elsewhere on the board
CLK_MAR: J3.6, U26.2 (CP), U27.2 (CP), U28.2 (CP), U29.2 (CP), U30.2 (CP), U32.2 (CP); also elsewhere on the board
CS_INH_EXT: J3.3, R5.2; also elsewhere on the board
CS_RAM_INH: U34.22 (~CE); also elsewhere on the board
GND: J3.1, R5.1, U22.8 (GND), U26.7 (CEP), U26.8 (GND), U26.10 (CET), U27.8 (GND), U28.7 (CEP), U28.8 (GND), U28.10 (CET), U29.8 (GND), U30.8 (GND), U31.16 (GND), U32.8 (GND), U34.2 (A16), U34.16 (GND), U43.8 (GND), U47.8 (GND), U47.15 (E), U51.8 (GND), U51.15 (E); also elsewhere on the board
unnamed: U27.15 (TC), U29.10 (CET)
unnamed: U29.15 (TC), U30.10 (CET)
unnamed: U30.15 (TC), U32.10 (CET)
unnamed: U3.11, U31.22 (~CE), U34.30 (CE2)
PC0: U47.3 (I1a); also elsewhere on the board
PC1: U47.13 (I1d); also elsewhere on the board
PC2: U47.6 (I1b); also elsewhere on the board
PC3: U47.10 (I1c); also elsewhere on the board
PC4: U51.3 (I1a); also elsewhere on the board
PC5: U51.13 (I1d); also elsewhere on the board
PC6: U51.6 (I1b); also elsewhere on the board
PC7: U51.10 (I1c); also elsewhere on the board
PC8: U43.3 (I1a); also elsewhere on the board
PC9: U43.13 (I1d); also elsewhere on the board
PC10: U43.6 (I1b); also elsewhere on the board
PC11: U43.10 (I1c); also elsewhere on the board
PC12: U22.3 (I1a); also elsewhere on the board
PC13: U22.13 (I1d); also elsewhere on the board
PC14: U22.6 (I1b); also elsewhere on the board
PC15: U22.10 (I1c); also elsewhere on the board
~CLK_PLS: U3.10; also elsewhere on the board
~RESET: J3.5, U26.1 (~MR), U27.1 (~MR), U28.1 (~MR), U29.1 (~MR), U30.1 (~MR), U32.1 (~MR); also elsewhere on the board
~RI: J3.32, U3.9; also elsewhere on the board
~RO: J3.31, U31.24 (~OE), U34.24 (~OE); also elsewhere on the board
~WE: U3.8, U31.31 (~WE), U34.29 (~WE); also elsewhere on the board

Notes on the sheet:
MEMORY ADDRESS REGISTER MSB
OR from VGA
MEMORY ADDRESS REGISTER LSB
RAM_ACTIVE
BANK REGISTER

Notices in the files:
hardware/redux-color-sound/cad/8-Bit CPU 32k.kicad_sch:
creativecommons.org/licenses/by-nc-sa/4.0
This work is licensed under CC BY-NC-SA 4.0
hardware/redux-color-sound/integrated/8-Bit CPU 32k.kicad_pcb:
Licensed under CC BY-NC-SA 4.0  http://creativecommons.org/licenses/by-nc-sa/4.0
hardware/redux-color-sound/integrated/Attribute.kicad_sch:
Derived from slu4 Redux; CC BY-NC-SA 4.0
